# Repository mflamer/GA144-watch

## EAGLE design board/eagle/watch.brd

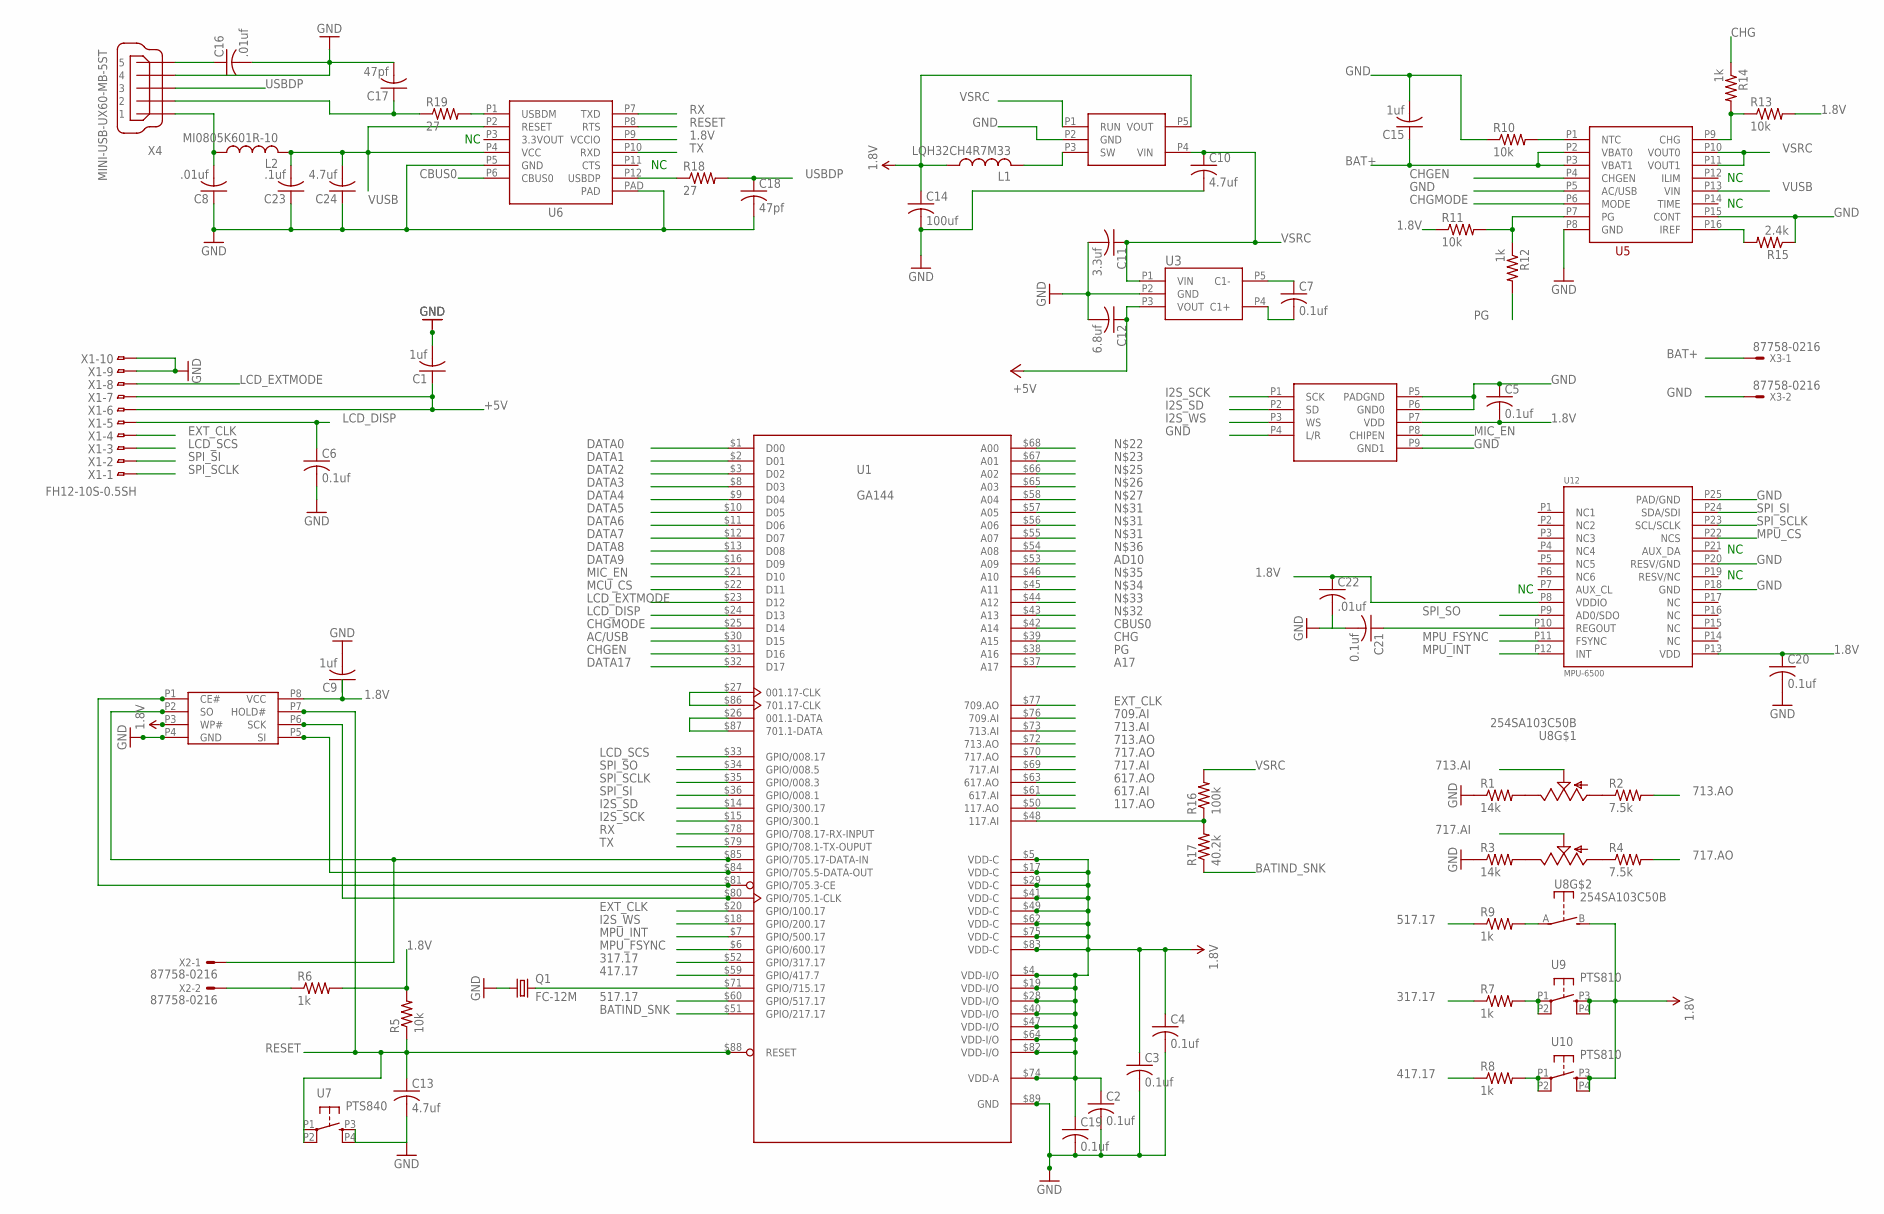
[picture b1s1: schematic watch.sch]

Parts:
C1, C9, C15: 1uf; C0402
C2, C3, C4, C5, C6, C7, C19, C20, C21: 0.1uf; C0402
C8, C16, C22: .01uf; C0402
C10, C13: 4.7uf; C0603
C11: 3.3uf; C0603
C12: 6.8uf; C0805
C14: 100uf; C1206
C17, C18: 47pf; C0402
C23: .1uf; C0402
C24: 4.7uf; C0402
L1: LQH32CH4R7M33; 1210
L2: MI0805K601R-10; C0805
Q1: FC-12M
R1, R3: 14k; R0402
R2, R4: 7.5k; R0402
R5, R10, R11, R13: 10k; R0402
R6, R7, R8, R9, R12, R14: 1k; R0402
R15: 2.4k; R0402
R16: 100k; R0402
R17: 40.2k; R0402
R18, R19: 27; R0402
U1: GA144; QFN88-0.4MM
U2: LTC3406-1.8; TSOT23
U3: LTC1517-5; TSOT23
U4: IS25WP128-JKLE; WSON8
U5: ISL9230; 16_LD_QFN
U6: FT234XD; DFN-12
U7: PTS840; PTS840GMPSMTRLFS
U8: 254SA103C50B
U9, U10: PTS810
U11: INMP441
U12: MPU-6500; QFN24-3
X1: FH12-10S-0.5SH
X2, X3: 87758-0216
X4: MINI-USB-UX60-MB-5ST; UX60-MB-5ST

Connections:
1.8V: C2.1, C3.1, C4.1, C5.2, C9.1, C14.1, C19.1, C20.1, C22.1, L1.P$1 (1), R5.2, R6.2, R11.1, R13.2, U1.$4 (VDD-I/O), U1.$5 (VDD-C), U1.$17 (VDD-C), U1.$19 (VDD-I/O), U1.$28 (VDD-I/O), U1.$29 (VDD-C), U1.$40 (VDD-I/O), U1.$41 (VDD-C), U1.$47 (VDD-I/O), U1.$49 (VDD-C), U1.$62 (VDD-C), U1.$64 (VDD-I/O), U1.$74 (VDD-A), U1.$75 (VDD-C), U1.$82 (VDD-I/O), U1.$83 (VDD-C), U2.P5 (VOUT), U4.P3 (WP#), U4.P8 (VCC), U6.P9 (VCCIO), U8.B, U9.P3 (S), U9.P4 (S1), U10.P3 (S), U10.P4 (S1), U11.P7 (VDD), U12.P8 (VDDIO), U12.P13 (VDD)
117.AO: U1.$50 (117.AO)
317.17: R7.1, U1.$52 (GPIO/317.17)
417.17: R8.1, U1.$59 (GPIO/417.7)
517.17: R9.1, U1.$60 (GPIO/517.17)
617.AI: U1.$61 (617.AI)
617.AO: U1.$63 (617.AO)
709.AI: U1.$76 (709.AI)
713.AI: U1.$73 (713.AI), U8.P2
713.AO: R2.2, U1.$72 (713.AO)
717.AI: U1.$69 (717.AI), U8.P2'
717.AO: R4.2, U1.$70 (717.AO)
+5V: C1.1, C12.1, U3.P3 (VOUT), X1.6, X1.7
A17: U1.$37 (A17)
AC/USB: U1.$30 (D15)
AD10: U1.$53 (A09)
AUX_CL: U12.P7 (AUX_CL)
AUX_DA: U12.P21 (AUX_DA)
BAT+: C15.1, U5.P2 (VBAT0), U5.P3 (VBAT1), X3.1
BATIND: R16.1, R17.2, U1.$48 (117.AI)
BATIND_SNK: R17.1, U1.$51 (GPIO/217.17)
CBUS0: U1.$42 (A14), U6.P6 (CBUS0)
CHG: R14.1, U1.$39 (A15)
CHGEN: U1.$31 (D16), U5.P4 (CHGEN)
CHGMODE: U1.$25 (D14), U5.P6 (MODE)
DATA0: U1.$1 (D00)
DATA1: U1.$2 (D01)
DATA2: U1.$3 (D02)
DATA3: U1.$8 (D03)
DATA4: U1.$9 (D04)
DATA5: U1.$10 (D05)
DATA6: U1.$11 (D06)
DATA7: U1.$12 (D07)
DATA8: U1.$13 (D08)
DATA9: U1.$16 (D09)
DATA17: U1.$32 (D17)
EXT_CLK: U1.$20 (GPIO/100.17), U1.$77 (709.AO), X1.4
GND: C1.2, C2.2, C3.2, C4.2, C5.1, C6.2, C8.1, C9.2, C10.2, C11.2, C12.2, C13.2, C14.2, C15.2, C16.2, C17.2, C18.2, C19.2, C20.2, C21.2, C22.2, C23.1, C24.1, Q1.1, R1.1, R3.1, R10.1, R15.1, U1.$89 (GND), U2.P2 (GND), U3.P2 (GND), U4.P4 (GND), U5.P5 (AC/USB), U5.P8 (GND), U5.P15 (CONT), U6.P5 (GND), U6.PAD, U7.P3 (S), U7.P4 (S1), U11.P4 (L/R), U11.P5 (PADGND), U11.P6 (GND0), U11.P9 (GND1), U12.P18 (GND), U12.P20 (RESV/GND), U12.P25 (PAD/GND), X1.9, X1.10, X3.2, X4.4
I2S_SCK: U1.$15 (GPIO/300.1), U11.P1 (SCK)
I2S_SD: U1.$14 (GPIO/300.17), U11.P2 (SD)
I2S_WS: U1.$18 (GPIO/200.17), U11.P3 (WS)
LCD_DISP: C6.1, U1.$24 (D13), X1.5
LCD_EXTMODE: U1.$23 (D12), X1.8
LCD_SCS: U1.$33 (GPIO/008.17), X1.3
MCU_CS: U1.$22 (D11)
MIC_EN: U1.$21 (D10), U11.P8 (CHIPEN)
MPU_CS: U12.P22 (NCS)
MPU_FSYNC: U1.$6 (GPIO/600.17), U12.P11 (FSYNC)
MPU_INT: U1.$7 (GPIO/500.17), U12.P12 (INT)
unnamed: R6.1, X2.2
unnamed: C7.1, U3.P5 (C1-)
unnamed: C7.2, U3.P4 (C1+)
unnamed: R10.2, U5.P1 (NTC)
unnamed: U1.$26 (001.1-DATA), U1.$87 (701.1-DATA)
unnamed: U1.$27 (001.17-CLK), U1.$86 (701.17-CLK)
unnamed: L1.P$2 (2), U2.P3 (SW)
unnamed: Q1.2, U1.$71 (GPIO/715.17)
unnamed: U1.$81 (GPIO/705.3-CE), U4.P1 (CE#)
unnamed: U1.$85 (GPIO/705.17-DATA-IN), U4.P2 (SO), X2.1
unnamed: R15.2, U5.P16 (IREF)
unnamed: C21.1, U12.P10 (REGOUT)
unnamed: R11.2, R12.1, U5.P7 (PG)
unnamed: R1.2, U8.P1
unnamed: R2.1, U8.P3
unnamed: R3.2, U8.P1'
unnamed: R4.1, U8.P3'
unnamed: R7.2, U9.P1, U9.P2 (P1)
unnamed: R8.2, U10.P1, U10.P2 (P1)
unnamed: R13.1, R14.2, U5.P9 (CHG)
unnamed: R9.2, U8.A
unnamed: C16.1, X4.5
unnamed: U1.$84 (GPIO/705.5-DATA-OUT), U4.P5 (SI)
PG: R12.2, U1.$38 (A16)
RESET: C13.1, R5.1, U1.$88 (RESET), U4.P7 (HOLD#), U6.P8 (RTS), U7.P1, U7.P2 (P1)
RESV/NC: U12.P19 (RESV/NC)
RX: U1.$78 (GPIO/708.17-RX-INPUT), U6.P7 (TXD)
SCK: U1.$80 (GPIO/705.1-CLK), U4.P6 (SCK)
SPI_SCLK: U1.$35 (GPIO/008.3), U12.P23 (SCL/SCLK), X1.1
SPI_SI: U1.$36 (GPIO/008.1), U12.P24 (SDA/SDI), X1.2
SPI_SO: U1.$34 (GPIO/008.5), U12.P9 (AD0/SDO)
TX: U1.$79 (GPIO/708.1-TX-OUPUT), U6.P10 (RXD)
USBDM: C17.1, R19.1, R19.2, U6.P1 (USBDM), X4.2
USBDP: C18.1, R18.1, R18.2, U6.P12 (USBDP), X4.3
VSRC: C10.1, C11.1, R16.2, U2.P1 (RUN), U2.P4 (VIN), U3.P1 (VIN), U5.P10 (VOUT0), U5.P11 (VOUT1)
VUSB: C8.2, C23.2, C24.2, L2.1, L2.2, U5.P13 (VIN), U6.P2 (RESET), U6.P4 (VCC), X4.1

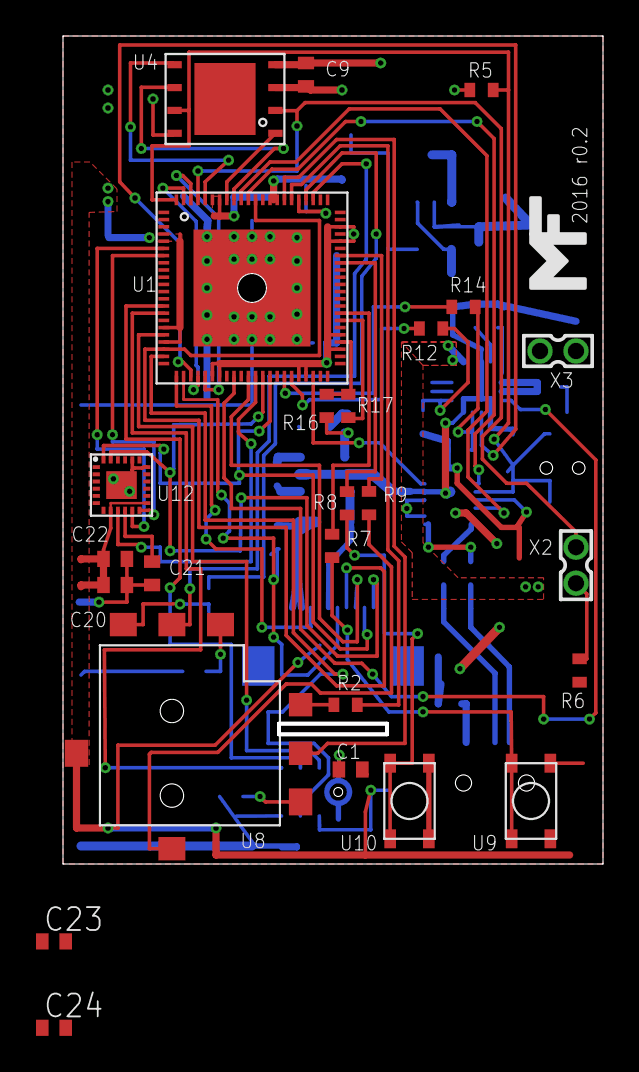
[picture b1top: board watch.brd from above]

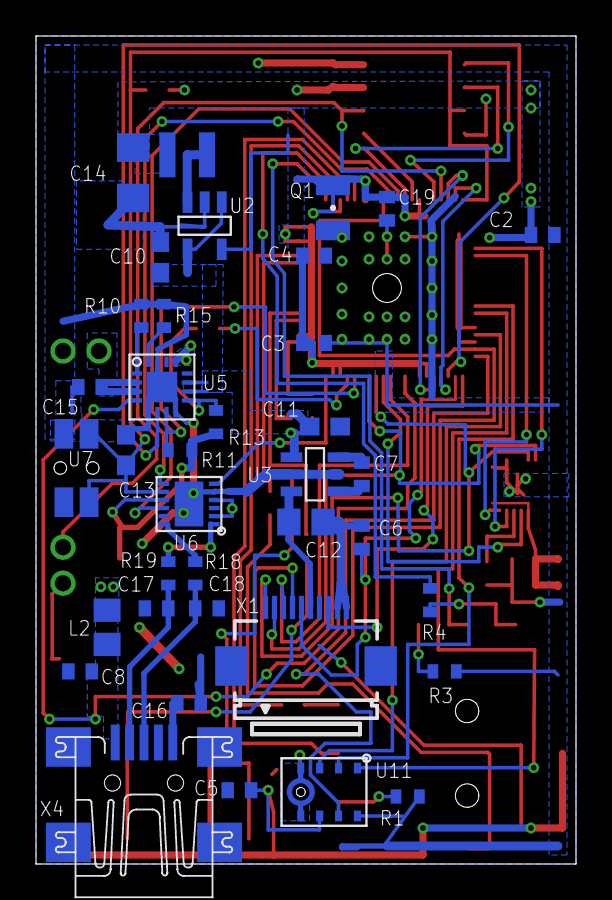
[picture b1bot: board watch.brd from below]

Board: 2 copper layers, 29.8 x 45.8 mm, 62 parts (37 on the bottom side), 62 nets.

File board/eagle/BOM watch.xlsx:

| BILL OF MATERIALS
 | ENTER Project Name , Version #
 | # | Designator | Quantity | Value | Footprint | Digi-Key (cut tape) | Manufacturer Part Number | Comments
 | 1 | C1,C9,C15 | 3 | 1uf | 0402 | 490-1320-1-ND | GRM155R60J105KE19D
 | 2 | C2,C3,C4,C5,C6,C7,C19,C20,C21 | 9 | 0.1uf | 0402 | 1276-1443-1-ND | CL05A104MP5NNNC
 | 3 | C8,C16,C22 | 3 | 0.01uf | 0402 | 490-4516-1-ND | GRM155R71H103KA88D
 | 4 | C10,C13 | 2 | 4.7uf | 0603 | 1276-2087-1-ND | CL10B475KQ8NQNC
 | 5 | C11 | 1 | 3.3uf | 0603 | 445-7476-1-ND | C1608X5R1C335K080AC
 | 6 | C12 | 1 | 6.8uf | 0805 | 399-3136-1-ND | C0805C685K9PACTU
 | 7 | C14 | 1 | 100uf | 1206 | 490-7217-1-ND | GRM31CR60J107ME39K
 | 8 | C17,C18 | 2 | 47pf | 0402 | 478-1078-1-ND | 04025A470JAT2A
 | 9 | U12 | 1 | ACCEL&GYRO | 24QFN | 1428-1011-1-ND | MPU-6500
 | 10 | Q1 | 1 | 32.768khz | 2-SMD | 535-10247-1-ND | ABS06-32.768KHZ-9-1-T
 | 11 | R1,R3 | 2 | 14k | 0402 | 311-14.0KLRCT-ND | RC0402FR-0714KL
 | 12 | R2,R4 | 2 | 7.5k | 0402 | 311-7.50KLRCT-ND | RC0402FR-077K5L
 | 13 | R5,R10,R11,R13 | 4 | 10k | 0402 | 311-10KJRCT-ND | RC0402FR-077K5L
 | 14 | R6,R7,R8,R9,R12,R14 | 6 | 1k | 0402 | 311-1.00KLRCT-ND | RC0402FR-071KL
 | 15 | R15 | 1 | 2.4k | 0402 | 311-2.4KJRCT-ND | RC0402JR-072K4L
 | 16 | R16 | 1 | 100k | 0402 | 311-100KLRCT-ND | RC0402FR-07100KL
 | 17 | R17 | 1 | 40.2k | 0402 | RMCF0402FT40K2CT-ND | RMCF0402FT40K2
 | 18 | U1 | 1 | MCU | QFN88-0.4MM | N/A | GA144-1.20 | http://www.greenarraychips.com/home/products/index.html
 | 19 | U2 | 1 | Stepdown | TSOT23 | LTC3406ES5#TRMPBFCT-ND | LTC3406ES5#TRMPBF
 | 20 | U3 | 1 | Booster | TSOT23 | LTC1517CS5-5#TRMPBFCT-ND | LTC1517CS5-5#TRMPBF
 | 21 | U4 | 1 | 128MB FLASH | 8-WSON | 706-1406-ND | IS25LP128-JKLE
 | 22 | U5 | 1 | Charger | 16QFN | ISL9230IRZ-TCT-ND | ISL9230IRZ-T
 | 23 | U6 | 1 | USB-UART | 12-DFN | 768-1178-1-ND | FT234XD-R
 | 24 | L1 | 1 | 4.7uh | 1210 | 490-6619-1-ND | LQH32CN4R7M33L
 | 25 | U7 | 1 | Button Right Angle | SM | CKN10514CT-ND | PTS840 GKP SMTR LFS
 | 26 | U8 | 1 | Joystick | SM | 254SA103B50B-ND | 254SA103B50B
 | 27 | U9,U10 | 2 | Button Top | SM | CKN10503CT-ND | PTS810 SJK 250 SMTR LFS
 | 28 | L2 | 1 | Ferrite Chip | 0805 | 240-2390-1-ND | MI0805K601R-10
 | 29 | U11 | 1 | Mic | SM | 1428-1014-1-ND | INMP441ACEZ-R7
 | 30 | X1 | 1 | FPC Conn 10 | SM | WM7978CT-ND | 0527461071
 | 31 | X2 | 1 | 2mm Header | Male | S5800-02-ND | NRPN021PAEN-RC
 | 33 | X4 | 1 | USB MINI B |  | H2959CT-ND | UX60-MB-5ST
 | 36
 | 38
 | 39
 | 40
 | 41
 | 42
 | 43
 | 44
 | 45
 | 46
 | 47
 | 48
 | 49
 | 50
 | 51
 | 52
 | 53
 | 54
 | 55
 | 56
 | 57
 | 58
 | 59
 | 60
 | 61
 | 62
 | 63
 | 64
 | 65
 | 66
 | 67
 | 68
 | 69
 | 70
 | 71
 | 72
 | 73
 | 74
 | 75
 | 76
 | 77
 | 78
 | 79
 | 80
 | 81
 | 82
 | 83
 | 84
 | 85
 | 86
 | 87
 | 88
 | 89
 | 90
 | 91
 | 92
 | 93
 | 94
 | 95
 | 96
 | 97
 | 98
 | 99
 | 100
 | 101
 | 102
 | 103
 | 104
 | 105
 | 106
 | 107
 | 108
 | 109
 | 110
 | 111
 | 112
 | 113
 | 114
 | 115
 | 116
 | 117
 | 118
 | 119
 | 120
 | 121
 | 122
 | 123
 | 124
 | 125
 | 126
 | 127
 | 128
 | 129
 | 130
 | 131
 | 132
 | 133
 | 134
 | 135
 | 136
 | 137
 | 138
 | 139
 | 140
 | 141
 | 142
 | 143
 | 144
 | 145

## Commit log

2017-06-21 create repo
2017-06-21 add image
2017-06-23 local copy of Bowman tool chain
2017-06-23 remove a few extra files
2017-06-23 remove another file
2017-08-26 initial support for graphics api
2017-08-26 send forever to avoid closing connection and chip reset
2017-08-26 remove old draw list node
2017-08-26 initialize rest of memory with empty list pointer values
2017-08-26 don't use shell option on linux
2017-09-11 update local copy of bowman tools
2017-09-11 Add initial jump if one is not provided in the prefix. Supports both the watch and vm code
2017-09-11 update to pass 4 args and receive 2 response words
2017-09-11 Add vm to watch code and delete conflicting watch nodes
2017-09-14 vm graphics interface node. support for new and update
2017-09-14 remove node 609 which is defined in nt.ga now
2017-09-14 graphics delete function
2017-09-17 Display datasheet and programming guide
2017-09-18 change sleep increment from 1s to 0.125s
2017-09-29 separate end-line word
2017-10-03 compile nodes in dependent order
2017-10-03 flash reads
2017-10-11 refactor display ram
2017-10-11 improve
2017-10-12 better display ram wire
2017-10-12 don't wait for update
2017-10-12 don' wait for delete
2017-10-12 start of an update mode
2017-10-22 support commands for sending pixels the primitive list
2017-10-24 clear display
2017-10-24 call update-row in update-display
2017-10-27 fix empty update case
2017-10-29 move wire nodes from nt.ga to watch.ga
2017-10-29 support for reading buttons
2017-10-29 move timing code to watch.ga
2017-11-01 support for wait
2017-11-17 VM joystick access
2017-11-17 sleep in 1/16 second increments
2018-11-20 add BOM
